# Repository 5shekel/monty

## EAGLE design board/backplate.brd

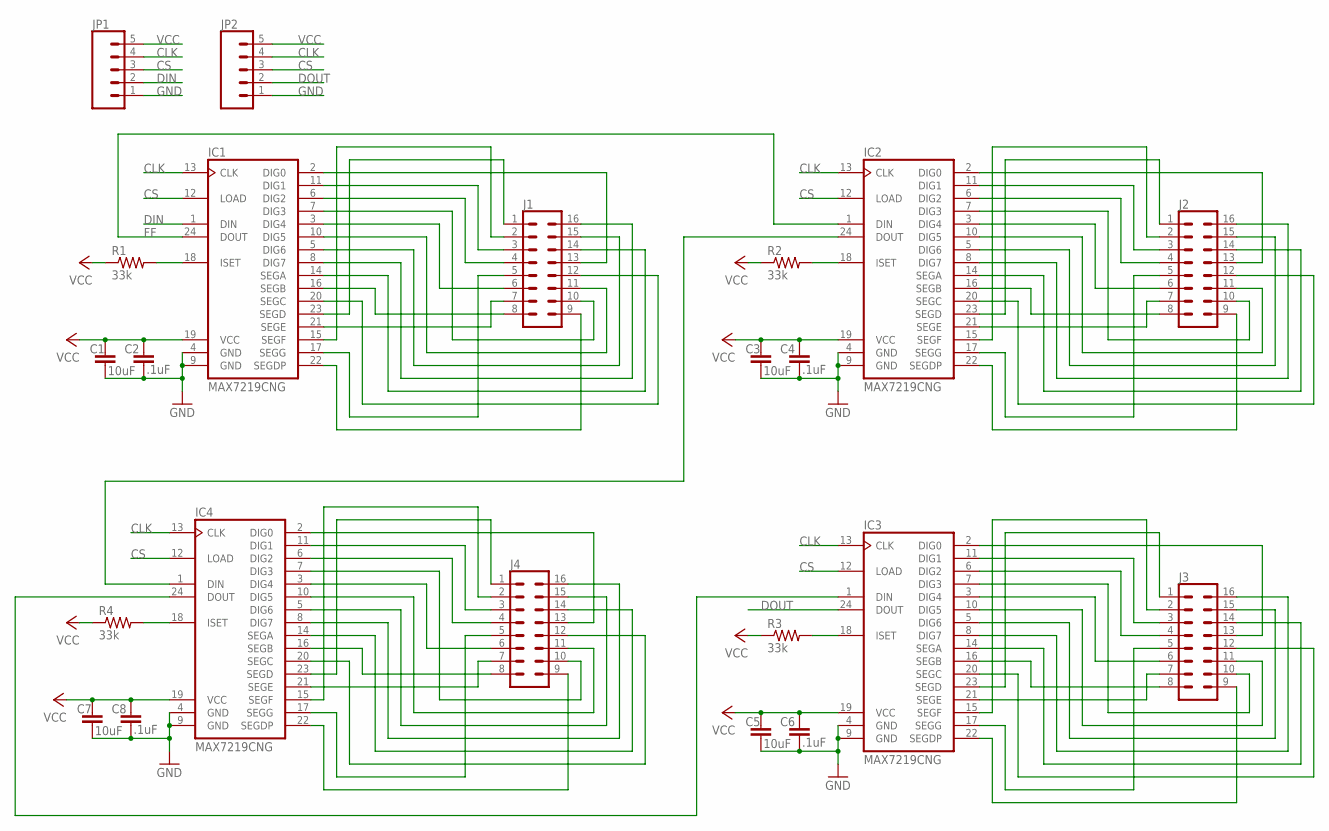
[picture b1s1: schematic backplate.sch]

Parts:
C1, C3, C5, C7: 10uF; 0805
C2, C4, C6, C8: .1uF; 0805
IC1, IC2, IC3, IC4: MAX7219CNG; DIL24-3
J1, J2, J3, J4: CONN_08X2IC; 2X8
JP1, JP2: CONN_05; 1X05
R1, R2, R3, R4: 33k; V526-0

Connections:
CLK: IC1.13 (CLK), IC2.13 (CLK), IC3.13 (CLK), IC4.13 (CLK), JP1.4, JP2.4
CS: IC1.12 (LOAD), IC2.12 (LOAD), IC3.12 (LOAD), IC4.12 (LOAD), JP1.3, JP2.3
DIN: IC1.1 (DIN), JP1.2
DOUT: IC3.24 (DOUT), JP2.2
FF: IC1.24 (DOUT), IC2.1 (DIN)
GND: C1.2, C2.2, C3.2, C4.2, C5.2, C6.2, C7.2, C8.2, IC1.4 (GND), IC1.9 (GND), IC2.4 (GND), IC2.9 (GND), IC3.4 (GND), IC3.9 (GND), IC4.4 (GND), IC4.9 (GND), JP1.1, JP2.1
unnamed: IC1.18 (ISET), R1.2
unnamed: IC1.2 (DIG0), J1.13 (8)
unnamed: IC1.11 (DIG1), J1.3 (5)
unnamed: IC1.6 (DIG2), J1.4 (7)
unnamed: IC1.7 (DIG3), J1.10 (14)
unnamed: IC1.3 (DIG4), J1.6 (11)
unnamed: IC1.10 (DIG5), J1.11 (12)
unnamed: IC1.5 (DIG6), J1.15 (4)
unnamed: IC1.8 (DIG7), J1.16 (2)
unnamed: IC1.14 (SEGA), J1.14 (6)
unnamed: IC1.16 (SEGB), J1.8 (15)
unnamed: IC1.20 (SEGC), J1.12 (10)
unnamed: IC1.23 (SEGD), J1.1
unnamed: IC1.21 (SEGE), J1.7 (13)
unnamed: IC1.15 (SEGF), J1.2 (3)
unnamed: IC1.17 (SEGG), J1.5 (9)
unnamed: IC1.22 (SEGDP), J1.9 (16)
unnamed: IC2.18 (ISET), R2.2
unnamed: IC2.2 (DIG0), J2.13 (8)
unnamed: IC2.11 (DIG1), J2.3 (5)
unnamed: IC2.6 (DIG2), J2.4 (7)
unnamed: IC2.7 (DIG3), J2.10 (14)
unnamed: IC2.3 (DIG4), J2.6 (11)
unnamed: IC2.10 (DIG5), J2.11 (12)
unnamed: IC2.5 (DIG6), J2.15 (4)
unnamed: IC2.8 (DIG7), J2.16 (2)
unnamed: IC2.14 (SEGA), J2.14 (6)
unnamed: IC2.16 (SEGB), J2.8 (15)
unnamed: IC2.20 (SEGC), J2.12 (10)
unnamed: IC2.23 (SEGD), J2.1
unnamed: IC2.21 (SEGE), J2.7 (13)
unnamed: IC2.15 (SEGF), J2.2 (3)
unnamed: IC2.17 (SEGG), J2.5 (9)
unnamed: IC2.22 (SEGDP), J2.9 (16)
unnamed: IC3.18 (ISET), R3.2
unnamed: IC3.2 (DIG0), J3.13 (8)
unnamed: IC3.11 (DIG1), J3.3 (5)
unnamed: IC3.6 (DIG2), J3.4 (7)
unnamed: IC3.7 (DIG3), J3.10 (14)
unnamed: IC3.3 (DIG4), J3.6 (11)
unnamed: IC3.10 (DIG5), J3.11 (12)
unnamed: IC3.5 (DIG6), J3.15 (4)
unnamed: IC3.8 (DIG7), J3.16 (2)
unnamed: IC3.14 (SEGA), J3.14 (6)
unnamed: IC3.16 (SEGB), J3.8 (15)
unnamed: IC3.20 (SEGC), J3.12 (10)
unnamed: IC3.23 (SEGD), J3.1
unnamed: IC3.21 (SEGE), J3.7 (13)
unnamed: IC3.15 (SEGF), J3.2 (3)
unnamed: IC3.17 (SEGG), J3.5 (9)
unnamed: IC3.22 (SEGDP), J3.9 (16)
unnamed: IC4.18 (ISET), R4.2
unnamed: IC4.2 (DIG0), J4.13 (8)
unnamed: IC4.11 (DIG1), J4.3 (5)
unnamed: IC4.6 (DIG2), J4.4 (7)
unnamed: IC4.7 (DIG3), J4.10 (14)
unnamed: IC4.3 (DIG4), J4.6 (11)
unnamed: IC4.10 (DIG5), J4.11 (12)
unnamed: IC4.5 (DIG6), J4.15 (4)
unnamed: IC4.8 (DIG7), J4.16 (2)
unnamed: IC4.14 (SEGA), J4.14 (6)
unnamed: IC4.16 (SEGB), J4.8 (15)
unnamed: IC4.20 (SEGC), J4.12 (10)
unnamed: IC4.23 (SEGD), J4.1
unnamed: IC4.21 (SEGE), J4.7 (13)
unnamed: IC4.15 (SEGF), J4.2 (3)
unnamed: IC4.17 (SEGG), J4.5 (9)
unnamed: IC4.22 (SEGDP), J4.9 (16)
unnamed: IC2.24 (DOUT), IC4.1 (DIN)
unnamed: IC3.1 (DIN), IC4.24 (DOUT)
VCC: C1.1, C2.1, C3.1, C4.1, C5.1, C6.1, C7.1, C8.1, IC1.19 (VCC), IC2.19 (VCC), IC3.19 (VCC), IC4.19 (VCC), JP1.5, JP2.5, R1.1, R2.1, R3.1, R4.1

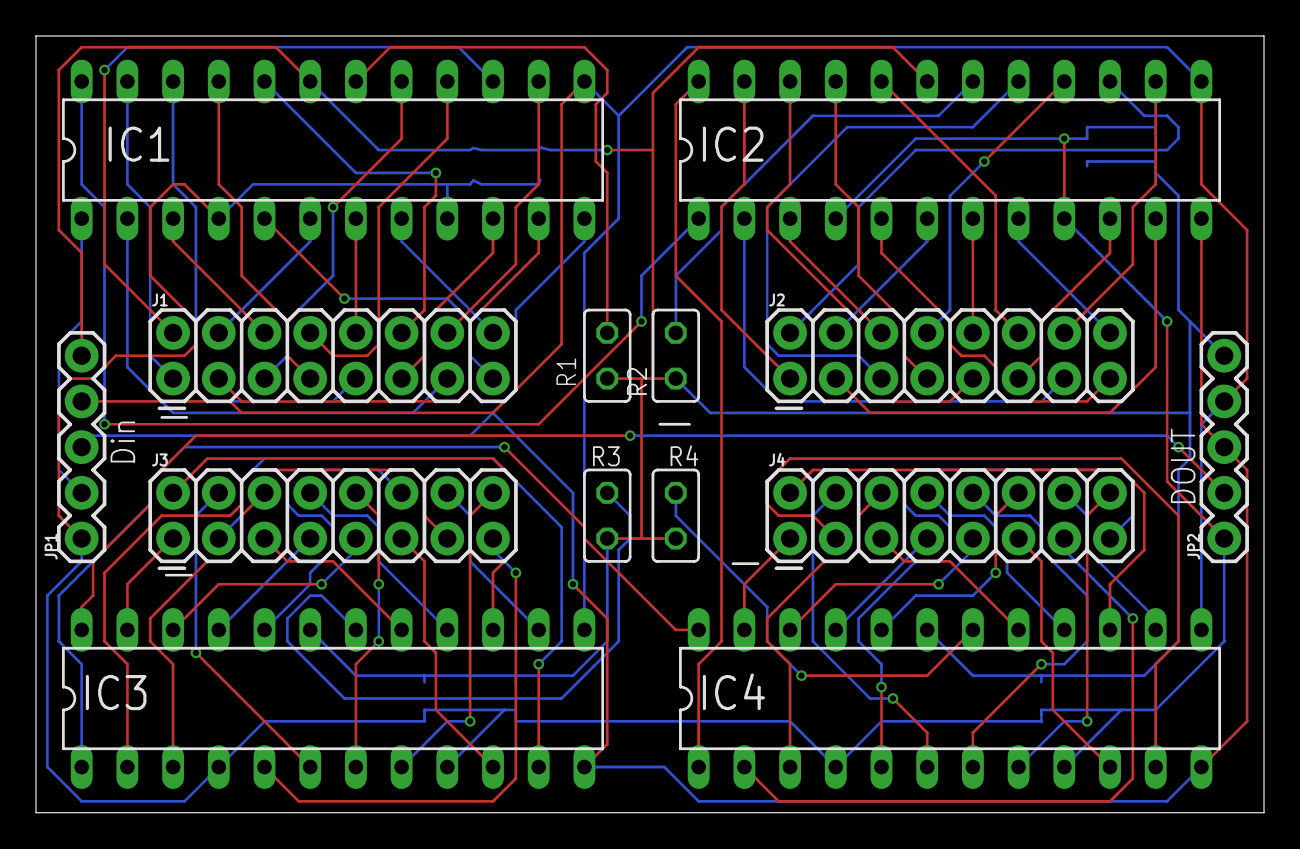
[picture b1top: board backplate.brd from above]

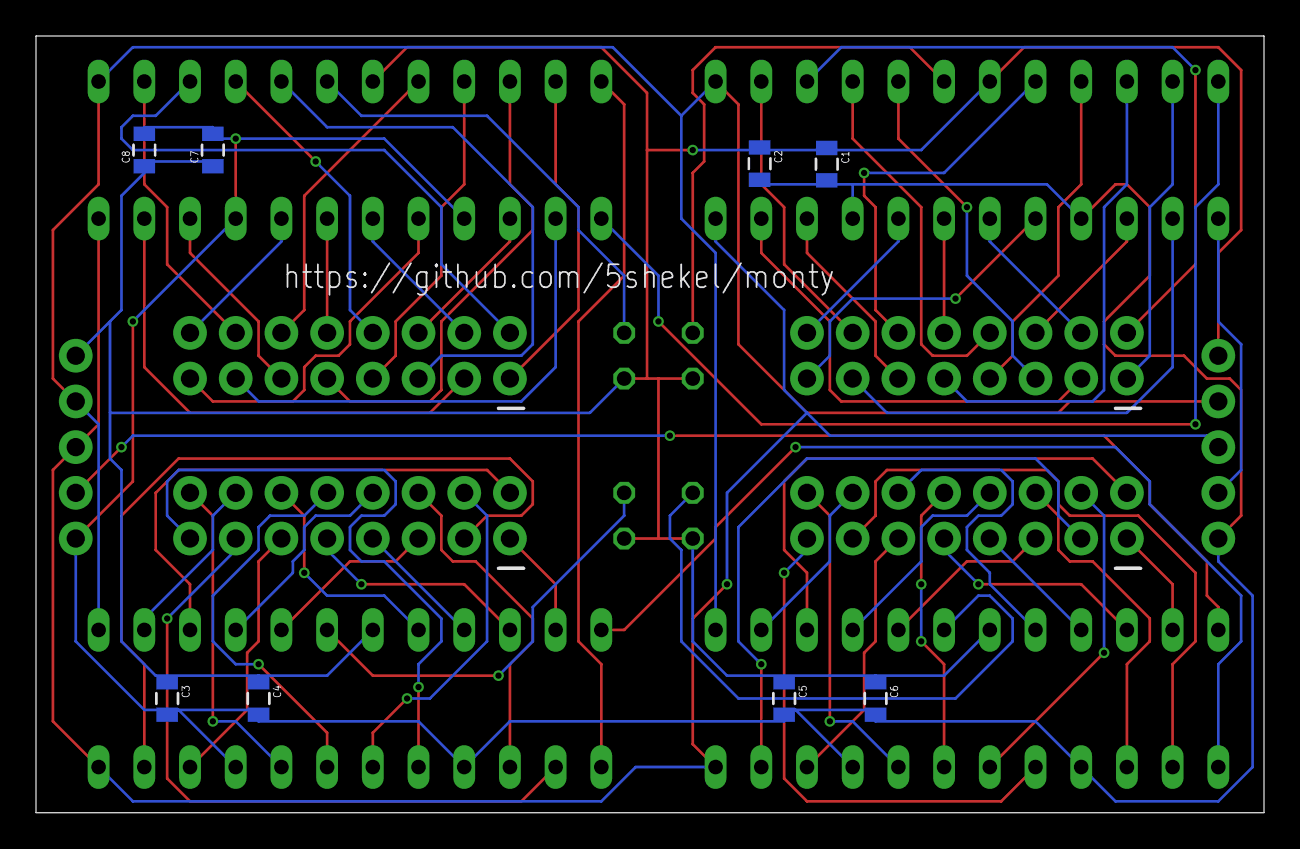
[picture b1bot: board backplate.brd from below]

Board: 2 copper layers, 68.2 x 43.2 mm, 22 parts (8 on the bottom side), 77 nets.

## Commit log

2018-04-19 Create monty4Eyes.ino
    copy from email, non working code
2018-04-19 format
2018-04-19 non working quad setup
2018-04-19 non working quad setup1 '
2018-04-19 compiles with include
2018-04-20 lean
2018-04-20 multi dim example
2018-04-22 works example one frame
2018-04-22 multi frame example
2018-04-23 split to folder
2018-04-23 2 animations
2018-04-23 functin works, low mem
2018-04-25 test code from Max72xxPanel.git
2018-04-25 dance test
2018-04-26 non block
2018-04-26 enum sorted
2018-04-28 explicit enum casting
2018-04-28 wiring coment
2018-04-29 looper
2018-04-29 eagle board
2018-04-29 add greber
2018-04-29 changed resistors to thru
2018-05-06 backplight v2
2018-05-07 based on https://i.imgur.com/TE96g29.png" "
2018-05-07 routed 4
2018-05-07 pdfs update
2018-05-07 4 routed
2018-05-18 works with cave wiring
